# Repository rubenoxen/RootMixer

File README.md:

# RootMixer 

A modular, bare-metal USB MIDI controller designed from scratch. Built around the STM32F411 (ARM Cortex-M4) using pure C CMSIS registers, featuring an expandable I2C and Analog Multiplexing architecture.

##  Features
* **Bare-Metal Firmware:** Zero heavy libraries (No HAL, No Arduino). Direct register manipulation for ultra-low latency (<2ms scan rate).
* **Hardware Multiplexing:** Daisy-chained `CD74HC4067` multiplexers allowing up to 16 analog channels per ADC pin.
* **Modular Design:** 1 Motherboard supports up to 4 swappable Channel Strips.
* **Native USB MIDI:** Implemented custom USB Device stack to interface natively with DAWs (Ableton, FL Studio) without drivers.
* **Real-time OSless Scheduler:** Custom `SysTick` non-blocking architecture.

##  Project Structure
* `/firmware`: Pure C source code, Makefile, and linker scripts.
* `/hardware`: KiCad 7 projects, Schematics (PDF), and Gerber files ready for JLCPCB.
    * `/Motherboard`: Main STM32 brain, LDO power supply, and Expansion ports.
    * `/Daughterboard_Channel`: The swappable channel strip (1x SC6021N Fader, 4x WH148 Pots, Mute Button).

##  Build & Flash (Firmware)
Requires `arm-none-eabi-gcc`, `make`, and `openocd`.

```bash
cd firmware
make clean
make
make flash
```

## License
This project is licensed under the MIT License - see the LICENSE file for details.

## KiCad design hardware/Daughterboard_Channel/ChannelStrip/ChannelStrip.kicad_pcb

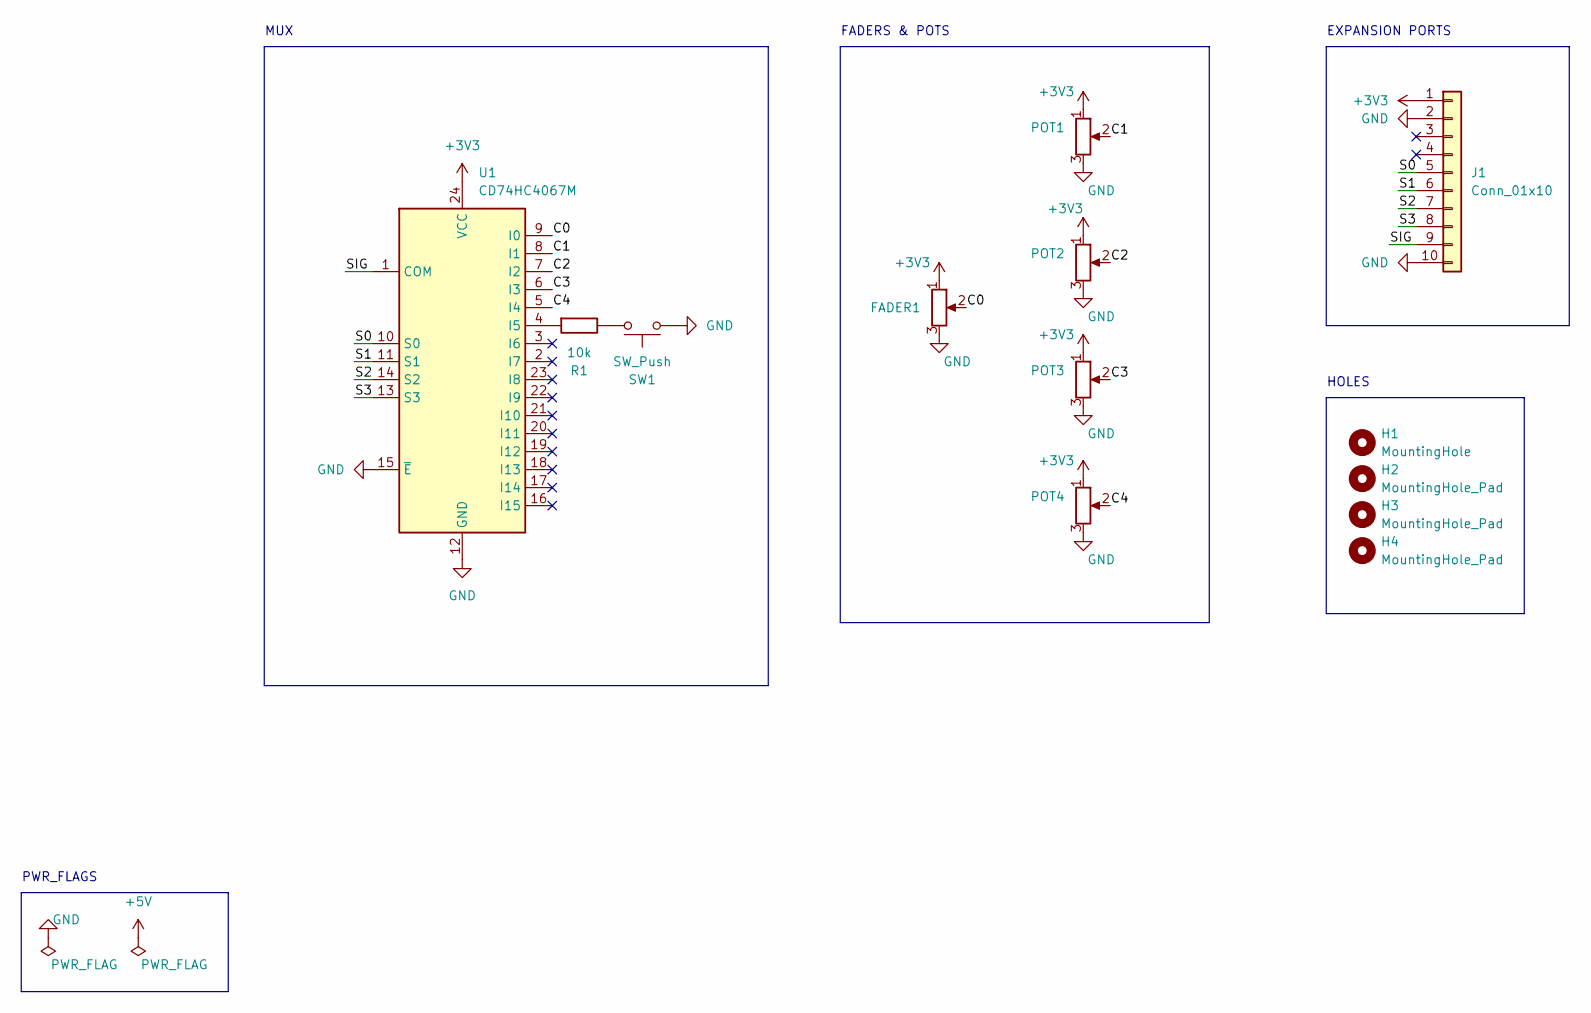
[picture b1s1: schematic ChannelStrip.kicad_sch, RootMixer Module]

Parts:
FADER1: POT1; Potentiometer_Bourns_PTA6043_Single_Slide
H1: MountingHole; MountingHole_2.2mm_M2_Pad_Via
H2, H3, H4: MountingHole_Pad; MountingHole_2.2mm_M2_Pad_Via
J1: Conn_01x10; PinHeader_1x10_P2.54mm_Vertical
POT1, POT2, POT3, POT4: POT1; Potentiometer_Bourns_PTV09A-1_Single_Vertical
R1: 10k; R_Axial_DIN0207_L6.3mm_D2.5mm_P10.16mm_Horizontal
SW1: SW_Push; SW_PUSH_6mm
U1: CD74HC4067M; SOIC-24W_7.5x15.4mm_P1.27mm

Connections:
+3V3: FADER1.1, J1.1, POT1.1, POT2.1, POT3.1, POT4.1, U1.24 (VCC)
/C0: FADER1.2, U1.9 (I0)
/C1: POT1.2, U1.8 (I1)
/C2: POT2.2, U1.7 (I2)
/C3: POT3.2, U1.6 (I3)
/C4: POT4.2, U1.5 (I4)
/S0: J1.5, U1.10 (S0)
/S1: J1.6, U1.11 (S1)
/S2: J1.7, U1.14 (S2)
/S3: J1.8, U1.13 (S3)
/SIG: J1.9, U1.1 (COM)
GND: FADER1.3, J1.2, J1.10, POT1.3, POT2.3, POT3.3, POT4.3, SW1.1, U1.12 (GND), U1.15 (~E)
unnamed: R1.1, SW1.2
unnamed: R1.2, U1.4 (I5)

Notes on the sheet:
FADERS & POTS
HOLES
PWR_FLAGS
EXPANSION PORTS
MUX

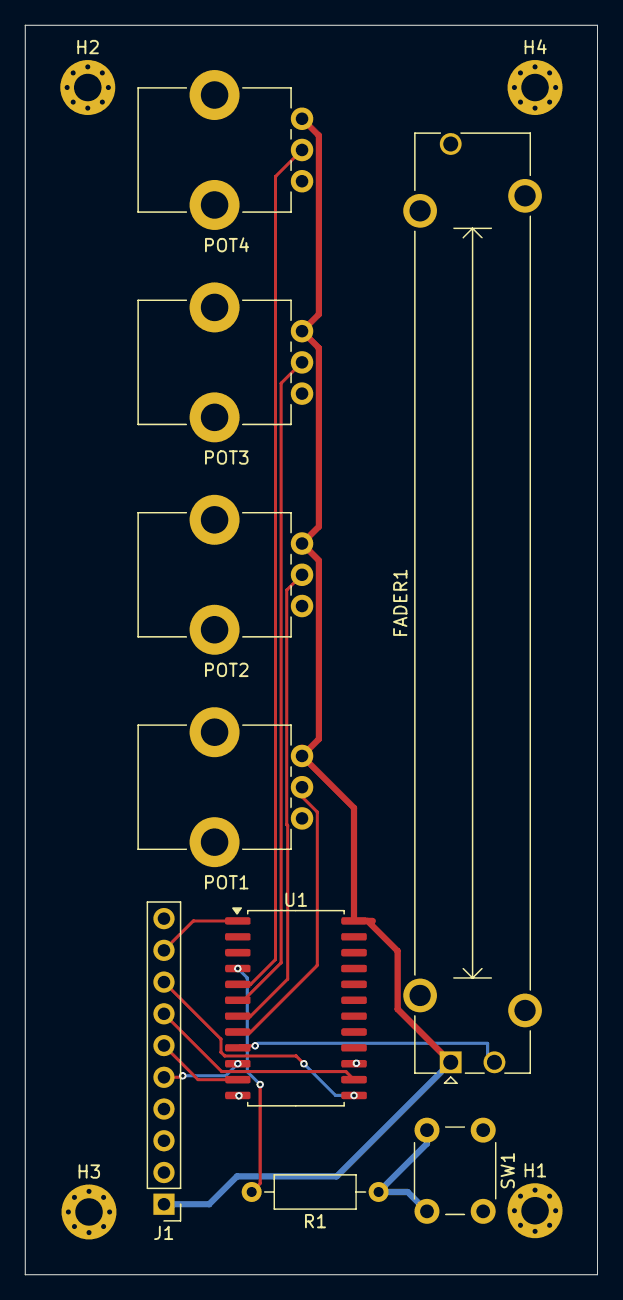
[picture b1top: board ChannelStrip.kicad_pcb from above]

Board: 2 copper layers, 45.8 x 100.0 mm, 13 parts (0 on the bottom side), 14 nets.

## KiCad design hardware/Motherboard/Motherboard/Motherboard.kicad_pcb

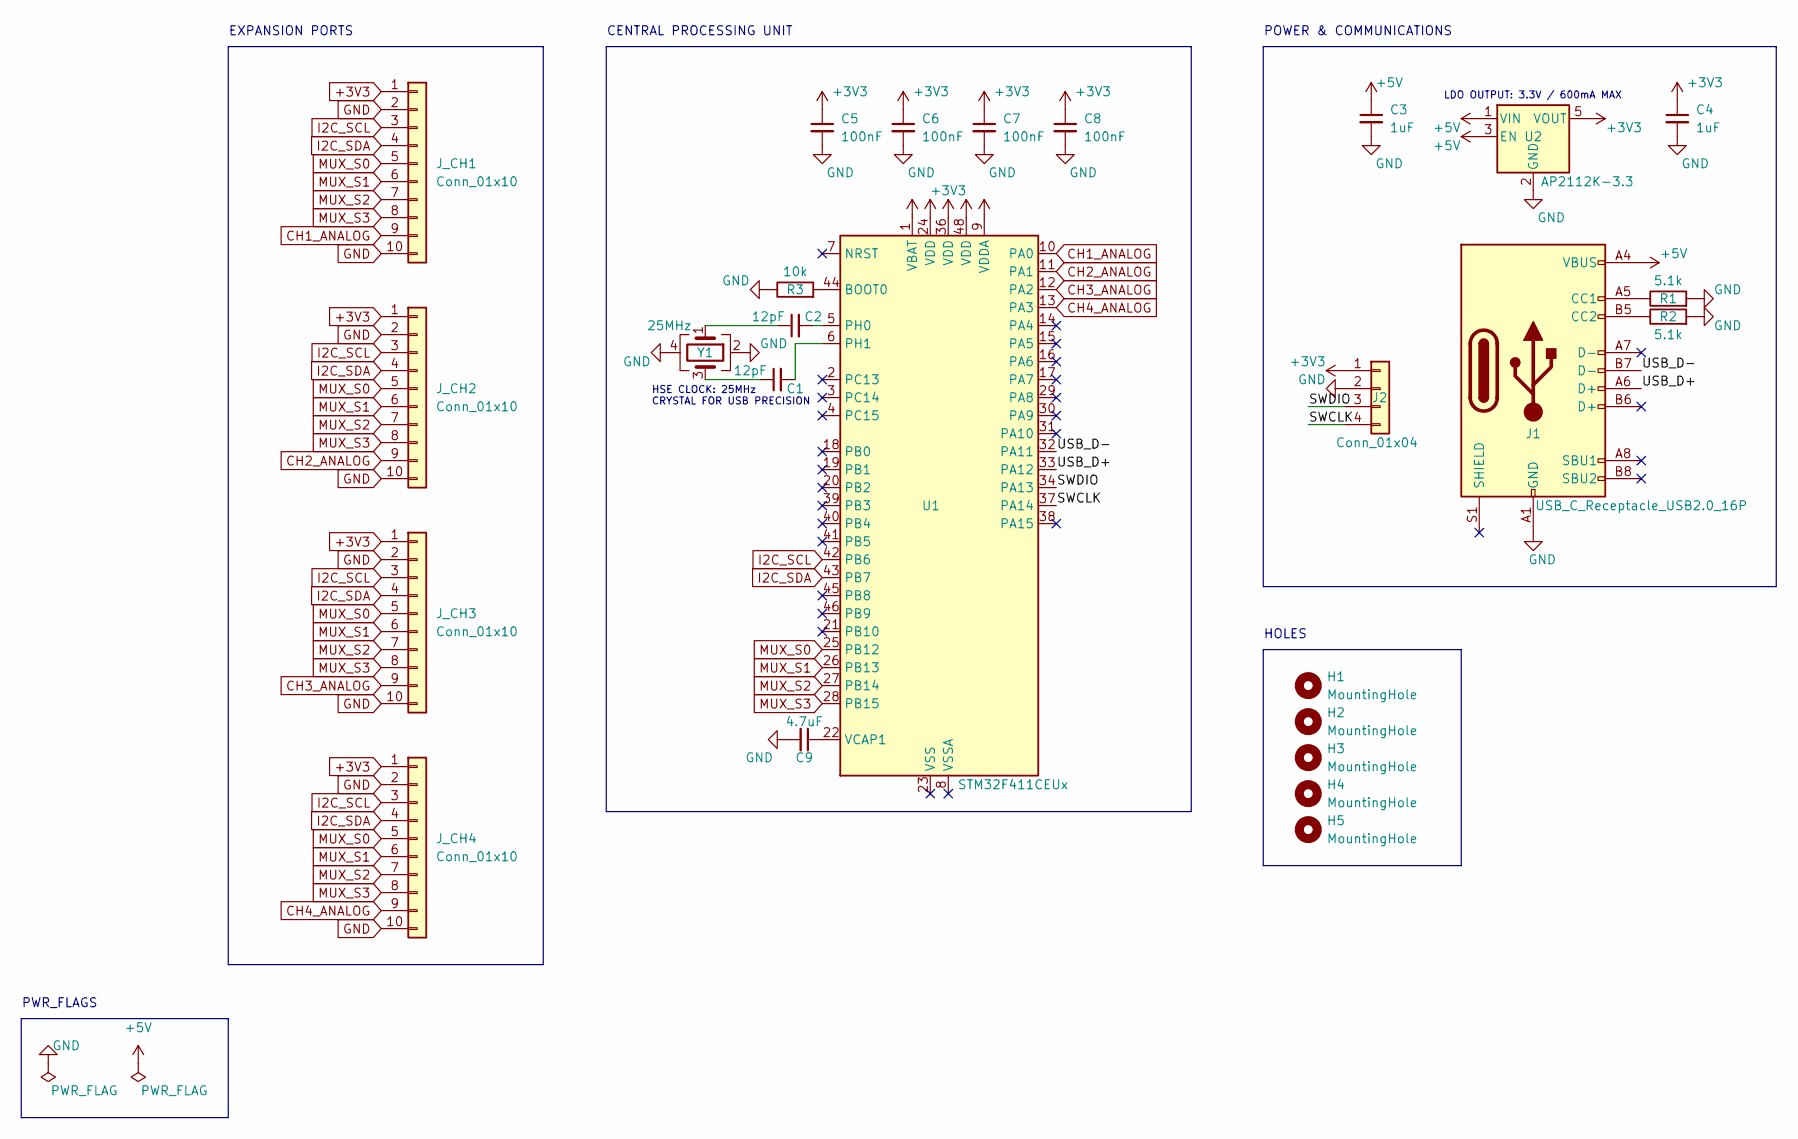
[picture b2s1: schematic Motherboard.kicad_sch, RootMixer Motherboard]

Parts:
C1, C2: 12pF; C_0603_1608Metric
C3, C4: 1uF; C_0603_1608Metric
C5, C6, C7, C8: 100nF; C_0603_1608Metric
C9: 4.7uF; C_0603_1608Metric
H1, H2, H3, H4, H5: MountingHole; MountingHole_2.2mm_M2_Pad_Via
J1: USB_C_Receptacle_USB2.0_16P; USB_C_Receptacle_HRO_TYPE-C-31-M-12
J2: Conn_01x04; PinHeader_1x04_P2.54mm_Vertical
J_CH1, J_CH2, J_CH3, J_CH4: Conn_01x10; Hirose_FH12-10S-0.5SH_1x10-1MP_P0.50mm_Horizontal
R1, R2: 5.1k; R_0603_1608Metric
R3: 10k; R_0603_1608Metric
U1: STM32F411CEUx; QFN-48-1EP_7x7mm_P0.5mm_EP5.6x5.6mm
U2: AP2112K-3.3; SOT-23-5
Y1: 25MHz; Crystal_SMD_3225-4Pin_3.2x2.5mm

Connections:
+3V3: C4.1, C5.1, C6.1, C7.1, C8.1, J2.1, J_CH1.1, J_CH2.1, J_CH3.1, J_CH4.1, U1.1 (VBAT), U1.9 (VDDA), U1.24 (VDD), U1.36 (VDD), U1.48 (VDD), U2.5 (VOUT)
+5V: C3.1, J1.A4 (VBUS), J1.A9 (VBUS), J1.B4 (VBUS), J1.B9 (VBUS), U2.1 (VIN), U2.3 (EN)
/SWCLK: J2.4, U1.37 (PA14)
/SWDIO: J2.3, U1.34 (PA13)
/USB_D+: J1.A6 (D+), U1.33 (PA12)
/USB_D-: J1.B7 (D-), U1.32 (PA11)
CH1_ANALOG: J_CH1.9, U1.10 (PA0)
CH2_ANALOG: J_CH2.9, U1.11 (PA1)
CH3_ANALOG: J_CH3.9, U1.12 (PA2)
CH4_ANALOG: J_CH4.9, U1.13 (PA3)
GND: C3.2, C4.2, C5.2, C6.2, C7.2, C8.2, C9.2, J1.A1 (GND), J1.A12 (GND), J1.B1 (GND), J1.B12 (GND), J2.2, J_CH1.2, J_CH1.10, J_CH2.2, J_CH2.10, J_CH3.2, J_CH3.10, J_CH4.2, J_CH4.10, R1.2, R2.2, R3.1, U2.2 (GND), Y1.2, Y1.4
I2C_SCL: J_CH1.3, J_CH2.3, J_CH3.3, J_CH4.3, U1.42 (PB6)
I2C_SDA: J_CH1.4, J_CH2.4, J_CH3.4, J_CH4.4, U1.43 (PB7)
MUX_S0: J_CH1.5, J_CH2.5, J_CH3.5, J_CH4.5, U1.25 (PB12)
MUX_S1: J_CH1.6, J_CH2.6, J_CH3.6, J_CH4.6, U1.26 (PB13)
MUX_S2: J_CH1.7, J_CH2.7, J_CH3.7, J_CH4.7, U1.27 (PB14)
MUX_S3: J_CH1.8, J_CH2.8, J_CH3.8, J_CH4.8, U1.28 (PB15)
unnamed: C1.1, Y1.3
unnamed: C2.1, Y1.1
unnamed: J1.A5 (CC1), R1.1
unnamed: J1.B5 (CC2), R2.1
unnamed: R3.2, U1.44 (BOOT0)
unnamed: C2.2, U1.5 (PH0)
unnamed: C1.2, U1.6 (PH1)
unnamed: C9.1, U1.22 (VCAP1)

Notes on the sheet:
HSE CLOCK: 25MHz CRYSTAL FOR USB PRECISION
LDO OUTPUT: 3.3V / 600mA MAX
EXPANSION PORTS
POWER & COMMUNICATIONS
HOLES
CENTRAL PROCESSING UNIT
PWR_FLAGS

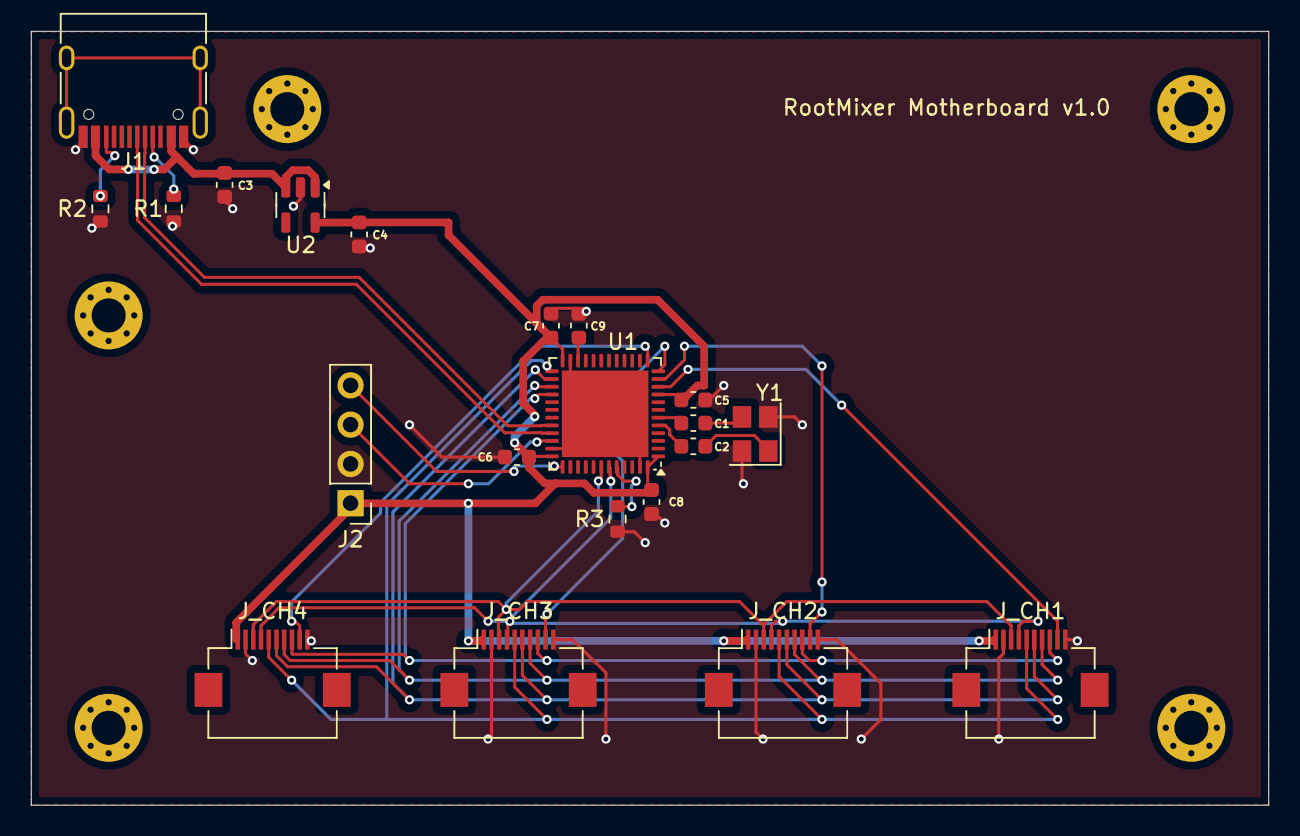
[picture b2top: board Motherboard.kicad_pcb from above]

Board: 2 copper layers, 80.0 x 50.0 mm, 26 parts (0 on the bottom side), 25 nets.

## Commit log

2026-04-11 new origins
2026-04-11 motherboardv0
2026-04-12 motherboardv1
2026-04-12 letsfirm
2026-04-12 geminimeodia
2026-04-12 usbdone
2026-04-13 yoqse
2026-04-13 tenemosfirmwarefamilia
2026-04-14 yoqse2
2026-04-14 portatilya
2026-04-16 sevelaluz
2026-04-16 sevelaluz2
2026-04-16 poniendorden
2026-04-16 Initialize README with project details and instructions
    Added project overview, features, structure, build instructions, and license information.
2026-04-16 Release v1.0: Hardware Schematics, BOM, Bare-Metal Firmware and MIT License
2026-04-16 Docs: Update README with badges and 3D render
2026-04-18 chasismadera
2026-05-02 hemos llegado a lo fisico, se jodio la marrana
2026-05-02 creo q lo tenemos
2026-05-02 esta bien por hoy

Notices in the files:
README.md:
License: MIT
